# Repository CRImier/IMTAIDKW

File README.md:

# IMTAIDKW
I Made This And I Don't Know Why - ESP-12 board with a 4-digit 7-segment display

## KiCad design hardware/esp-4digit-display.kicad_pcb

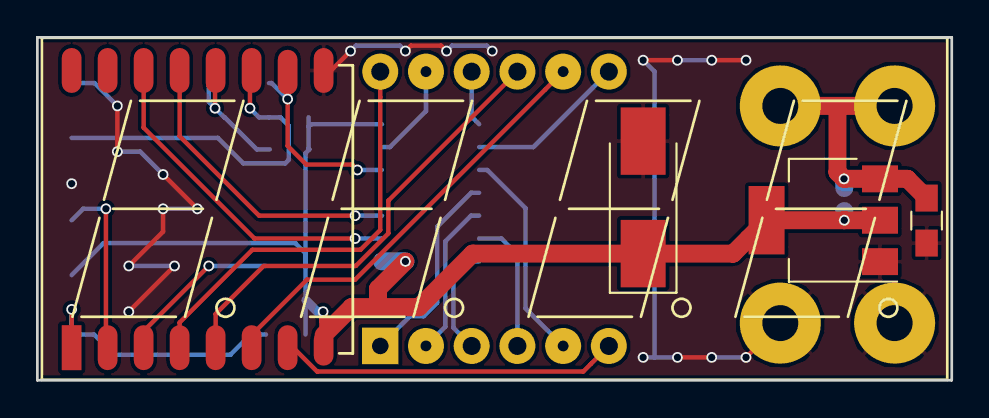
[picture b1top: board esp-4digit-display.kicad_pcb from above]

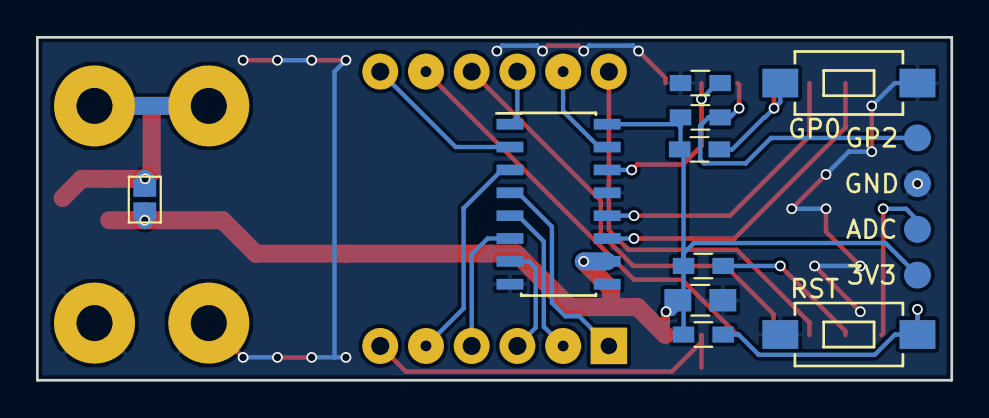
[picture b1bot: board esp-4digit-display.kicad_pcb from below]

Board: 2 copper layers, 50.8 x 19.0 mm, 21 parts (14 on the bottom side), 23 nets.

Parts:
AFF1: CA56-12; Cx56-12
C1: C_Small; C_0805_HandSoldering
C2: 100nF; C_0805_HandSoldering
C3: 100uF; CP_Tantalum_Case-C_EIA-6032-28_Hand
JP1: JUMPER; GS2
R1, R2, R3, R4, R5: 10K; R_0603_HandSoldering
SW1: GP0; SW_SPST_EVQPE1
SW2: RST; SW_SPST_EVQPE1
U1: LM1117-3.3; SOT-223
U2: ESP-12
U3: 74HC595; SOIC-16_3.9x9.9mm_Pitch1.27mm
W1: ADC; Measurement_Point_Round-SMD-Pad_Small
W2: GND; Measurement_Point_Round-SMD-Pad_Small
W3: 5V; SolderWirePad_2x_2mmDrill
W4: GND; SolderWirePad_2x_2mmDrill
W5: 3V3; Measurement_Point_Round-SMD-Pad_Small
W6: GP2; Measurement_Point_Round-SMD-Pad_Small

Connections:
+3V3: C2.1, C3.1, JP1.2, R1.1, R2.1, R3.2, R4.2, U1.2, U1.4, U2.8, U3.10, U3.16, W5.1
+5V: C1.1, JP1.1, U1.3, W3.1
C1: AFF1.12, U2.4
C2: AFF1.9, U2.5
C3: AFF1.8, U2.6
C4: AFF1.6, U2.7
CLOCK: U2.14, U3.11
DATA: R5.2, U2.10, U3.14
GND: C1.2, C2.2, C3.2, R5.1, SW1.2, SW2.2, U1.1, U2.9, U3.8, U3.13, W2.1, W4.1
GPIO0: R1.2, SW1.1, U2.12
LATCH: U2.13, U3.12
unnamed: R3.1, U2.3
unnamed: R4.1, U2.11, W6.1
unnamed: U2.2, W1.1
R1: AFF1.11, U3.15
R2: AFF1.3, U3.7
R3: AFF1.4, U3.6
R4: AFF1.2, U3.5
R5: AFF1.1, U3.4
R6: AFF1.5, U3.3
R7: AFF1.7, U3.2
R8: AFF1.10, U3.1
RST: R2.2, SW2.1, U2.1

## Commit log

2017-06-20 Adding hardware and software gitignores
2017-06-20 Adding hardware files for the current revision
2017-06-20 Updated schematic with bit-to-digit mapping
2017-07-09 Added sample script - broadcasts poop emoji and shows "1337" on display
2017-07-09 Ported shiftOut to Viper
2017-07-09 Ported shiftOut to Viper (left in a statement from experimentation, removed)
2017-07-23 Oh wait forgot this shit
2017-07-23 Fuck it I don't wanna go over this code I'll post is as it is
2017-07-24 Ducktaping shit together
2019-10-22 WIP countdown timer
2019-10-27 Debugged the countdown script - display is now flicker-free, but time countdown is delayed by ~7 seconds each minute, weird.
2019-11-04 Adding the button read and "decrement time by 10 minutes on button press" function
2019-11-04 Switching to pure-Python-bitbanging - with the coefficients in run() definition, gives flicker-free operation
2019-11-04 Adding the firmware image of v1.9.2 where ESP8266 timekeeping patches are applied and README explaining that.
